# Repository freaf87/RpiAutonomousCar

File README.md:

Rpi Autonomous Car PCB 
====================
This board bring those additional functions below to the Raspberry pi:

	 - Analog Digital Converter with MCP3008 (8)
	 - DC Brushed Motor driver (2) with TB6612FNG
	 - Level converted IOs (5V <-> 3.3V) (8)
     - 16-channel, 12-bit PWM with PCA9685
     - RGB LED (1)
     - Pushbutton (1)

Top                                                                      |  Bottom
:-----------------------------------------------------------------------:|:--------------------------------------------------------------:
  |  

Author: Frederic Afadjigla, 2018

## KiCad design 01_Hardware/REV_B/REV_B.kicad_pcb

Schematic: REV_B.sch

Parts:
C1, C3: 100n; C_0603_1608Metric
C2: 10u; CP_Elec_4x4.5
C4, C5, C6, C7, C8, C9, C10, C11, C13: 10n; C_0603_1608Metric
C12: 0.33u; C_0603_1608Metric
J1: RaspberryPi; PinSocket_2x20_P2.54mm_Vertical
J2, J3, J4: Conn_01x02; Molex_KK-254_AE-6410-02A_1x02_P2.54mm_Vertical
J5: Conn_01x08; PinHeader_1x08_P2.54mm_LongPad_Vertical_SMD_Pin1Right
J6: Conn_02x04_Counter_Clockwise; PinHeader_2x04_P2.54mm_Vertical_SMD
J7, J8, J9, J10, J11, J12: Conn_01x03; PinHeader_1x03_P2.54mm_Vertical
J13: Conn_01x08; PinHeader_1x08_P2.54mm_Vertical
J14: Conn_01x01; PinSocket_1x01_P2.54mm_Vertical
JP1: Jumper_3_Open; SolderJumper-3_P1.3mm_Open_RoundedPad1.0x1.5mm
R1, R2, R3, R4, R10, R11, R12, R13, R48: 1k; R_0603_1608Metric
R5, R6, R7, R8, R9, R30, R31, R32, R33, R34, R35, R36, R37, R38, R39, R40, R41, R42, R43, R44, R45: 10k; R_0603_1608Metric
R14, R15, R16, R17: 22k; R_0603_1608Metric
R18, R19, R20, R21, R22, R23, R24, R25, R26, R27, R28, R29, R46, R47: 220; R_0603_1608Metric
SW1: SW_Push; SW_PUSH_6mm
U1: TB6612FNG; SSOP-24_5.3x8.2mm_P0.65mm
U2: MCP3008; SOIC-16_3.9x9.9mm_P1.27mm
U3: PCA9685PW; TSSOP-28_4.4x9.7mm_P0.65mm
U4, U5, U6, U7: BSS138PS; SOT-363_SC-70-6
U8: L7805; TO-252-3_TabPin2
U9: ASMT-YTB7-0AA02; LED_Avago_PLCC6_3x2.8mm

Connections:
+3V3: C1.1, J1.1, J1.17, J11.1, J11.2, J11.3, R30.1, R31.1, R32.1, R33.1, R34.1, R35.1, R36.1, R37.1, SW1.2, U1.20, U2.15 (Vref), U2.16 (Vdd), U4.2, U4.5, U5.2, U5.5, U6.2, U6.5, U7.2, U7.5
+5V: C13.1, J1.2, J1.4, J7.2, J8.2, J9.2, J10.1, J10.2, J10.3, JP1.3, R38.1, R39.1, R40.1, R41.1, R42.1, R43.1, R44.1, R45.1, U3.3, U3.5, U3.28, U8.3
+BATT: C2.1, C3.1, C12.1, J2.2, J14.1, U1.13, U1.14, U1.24, U8.1
GND: C1.2, C2.2, C3.2, C4.2, C5.2, C6.2, C7.2, C8.2, C9.2, C10.2, C11.2, C12.2, C13.2, J1.6, J1.9, J1.14, J1.20, J1.25, J1.30, J1.34, J1.39, J2.1, J7.3, J8.3, J9.3, J12.1, J12.2, J12.3, JP1.1, R1.2, R2.2, R3.2, R4.2, R5.2, R6.2, R7.2, R8.2, R9.1, U1.3, U1.4, U1.9, U1.10, U1.18, U2.9 (DGND), U2.14 (AGND), U3.1, U3.2, U3.4, U3.14, U3.25, U8.2, U9.1, U9.2, U9.3
I2C1_SCL_HV: J13.2, R43.2, U3.26, U5.3
I2C1_SCL_LV: J1.5, R33.2, U5.4
I2C1_SDA_HV: J13.1, R39.2, U3.27, U5.6
I2C1_SDA_LV: J1.3, R32.2, U5.1
unnamed: C4.1, R1.1, R10.2, U2.1 (CH0)
unnamed: C5.1, R2.1, R11.2, U2.2 (CH1)
unnamed: C6.1, R3.1, R12.2, U2.3 (CH2)
unnamed: C7.1, R4.1, R13.2, U2.4 (CH3)
unnamed: C8.1, R5.1, R14.2, U2.5 (CH4)
unnamed: C9.1, R6.1, R15.2, U2.6 (CH5)
unnamed: C10.1, R7.1, R16.2, U2.7 (CH6)
unnamed: C11.1, R8.1, R17.2, U2.8 (CH7)
unnamed: J1.24, U2.10 (~CS~/SHDN)
unnamed: J1.32, U1.23
unnamed: J1.33, U1.15
unnamed: J1.35, U1.21
unnamed: J1.36, U1.22
unnamed: J1.37, U1.17
unnamed: J1.38, U1.16
unnamed: J1.40, U1.19
unnamed: J3.1, U1.1, U1.2
unnamed: J3.2, U1.5, U1.6
unnamed: J4.1, U1.11, U1.12
unnamed: J4.2, U1.7, U1.8
unnamed: J5.1, R10.1
unnamed: J5.2, R11.1
unnamed: J5.3, R12.1
unnamed: J5.4, R13.1
unnamed: J5.5, R14.1
unnamed: J5.6, R15.1
unnamed: J5.7, R16.1
unnamed: J5.8, R17.1
unnamed: J6.1, R21.1
unnamed: J6.2, R22.1
unnamed: J6.3, R23.1
unnamed: J6.4, R24.1
unnamed: J6.5, R25.1
unnamed: J6.6, R26.1
unnamed: J6.7, R27.1
unnamed: J6.8, R28.1
unnamed: J7.1, R47.1
unnamed: J8.1, R46.1
unnamed: J9.1, R29.1
unnamed: J13.3, R38.2, U4.6
unnamed: J13.4, R42.2, U4.3
unnamed: J13.5, R40.2, U6.6
unnamed: J13.6, R44.2, U6.3
unnamed: J13.7, R41.2, U7.6
unnamed: J13.8, R45.2, U7.3
unnamed: JP1.2, U3.24
unnamed: R9.2, U3.23
unnamed: R18.1, U9.6
unnamed: R18.2, U3.22
unnamed: R19.1, U9.5
unnamed: R19.2, U3.21
unnamed: R20.1, U9.4
unnamed: R20.2, U3.20
unnamed: R21.2, U3.6
unnamed: R22.2, U3.7
unnamed: R23.2, U3.8
unnamed: R24.2, U3.9
unnamed: R25.2, U3.10
unnamed: R26.2, U3.11
unnamed: R27.2, U3.12
unnamed: R28.2, U3.13
unnamed: R29.2, U3.15
unnamed: R46.2, U3.16
unnamed: R47.2, U3.17
unnamed: R48.2, SW1.1
PUSH_BUTTON: J1.22, R48.1
SPI0_CLK_LV: J1.23, R34.2, U2.13 (CLK), U6.1
SPI0_CS1_LV: J1.26, R35.2, U6.4
SPI0_MISO_LV: J1.21, R31.2, U2.12 (Dout), U4.4
SPI0_MOSI_LV: J1.19, R30.2, U2.11 (Din), U4.1
UART_RX_LV: J1.10, R37.2, U7.4
UART_TX_LV: J1.8, R36.2, U7.1

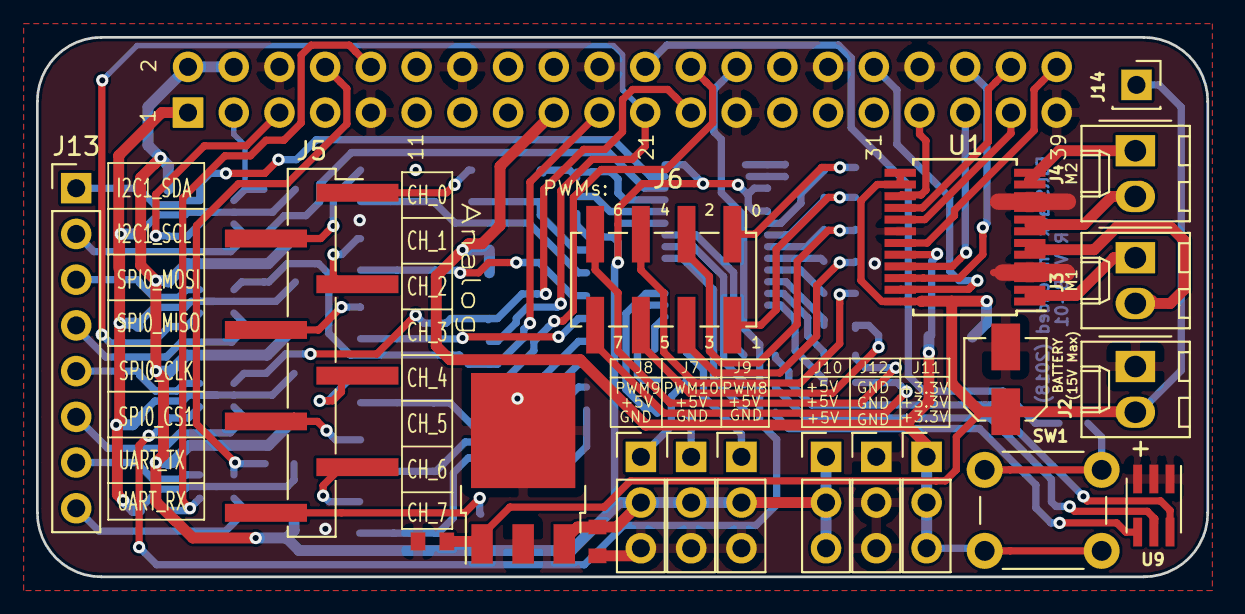
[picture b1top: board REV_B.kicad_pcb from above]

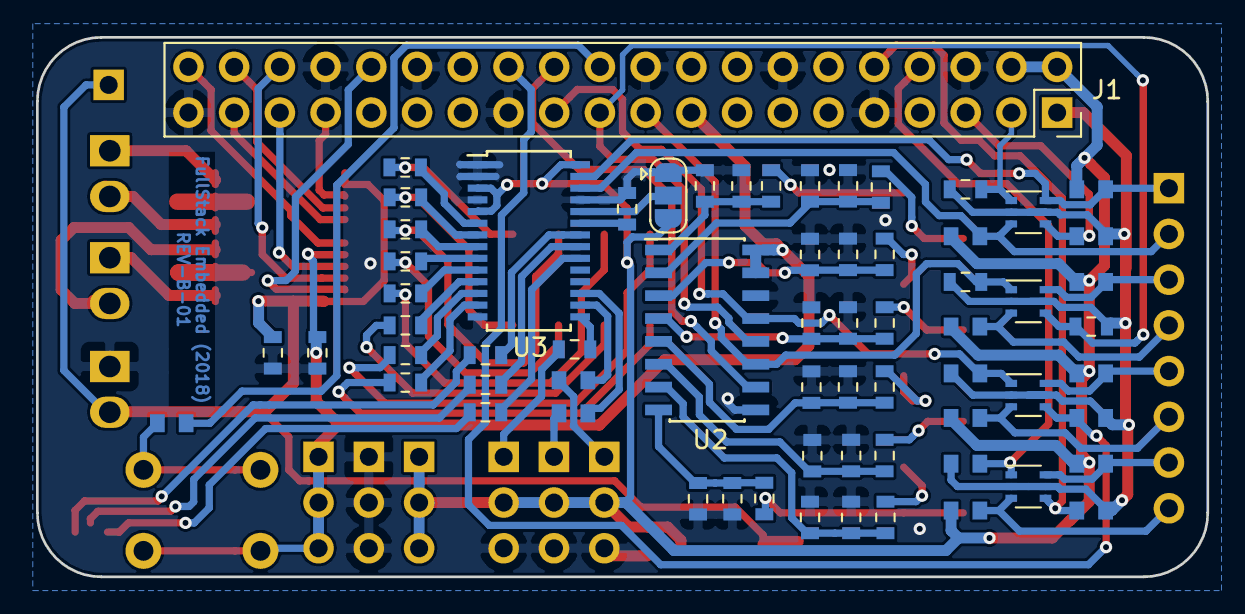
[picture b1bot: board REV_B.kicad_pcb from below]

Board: 2 copper layers, 65.0 x 30.0 mm, 86 parts (66 on the bottom side), 80 nets.

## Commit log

2017-05-01 routing...
2017-05-13 routing
2017-05-26 routing ...
2017-05-29 rounting/Pinout minor changes
2017-05-29 routing almost done
2017-05-30 routing done
2017-06-05 ready for review
2017-06-07 routing done. Ready to order
2017-06-10 Version 1 done
2017-06-11 Hardware Documentation added
2017-06-13 Documenting...
2017-06-17 Restructure Directories
2017-06-18 add cost calculation
2017-06-24 driver HCSR04 LED MCP3004 TB6612FNG added
2017-06-24 moinor corrections
2017-06-24 servo driver added
2017-06-28 add simple autonomous program
2017-07-09 Remote control added
2017-08-05 minor changes
2017-08-18 Docu actualised
2017-09-15 Thread based Line follower added
2017-09-23 Line follower (continued)
2017-10-28 Refactor and add TODOs
2017-10-28 Add test of drive function
2017-10-28 Implement turning
2017-10-29 Add ultrasonic current measurement property
2017-10-29 Add obstacle detection test
2017-10-29 Add curve driving function
2017-10-29 Add option to skip tests
2017-10-30 Hardware PWM support
2017-10-31 Add shebangs, encoding and license headers
2017-10-31 Use new API for autonomous driving
2017-10-31 Use continuous drive mode
2017-10-31 Rename for PEP8
2017-10-31 Perform complete rotation to keep from tangling code in test
2017-10-31 Remove unused file
2017-10-31 Refactor ultrasonic ranger
2017-10-31 Migrate to wiringpi
2017-11-02 Call builtin debug rather than self-made
2017-11-02 Establish connection within Receiver class
2017-11-02 Move connection closing into class
2017-11-02 Have class start thread on its own
2017-11-02 Simplify command sending logic
2017-11-02 Close connection through context manager
2017-11-02 PEP8 and light refactor of LED
2017-11-02 Move GPIO bookkeeping into superclass
2017-11-02 Subclass LED to GPIO_Manager
2017-11-02 Factor distance measurements into properties
2017-11-02 Migrate infrared sensor to subclass GPIO_Manager
2017-11-02 Move hardware modules into their own package
2017-11-04 Use INPUT/OUTPUT constants from wiringpi
2017-11-04 Use __exit__ rather than destroy methods
2017-11-04 Migrate to motor_driver to wiringpi
2017-11-04 Add LED test, reorganize controllers
2017-11-04 Roll code into package
2017-11-04 HW Pwm modifications
2017-11-04 Insert headers, rename files
2017-11-04 Refactor LineFollowers
2017-11-05 Refactor ADC code
2017-11-05 Use Robot in LineFollower
2017-11-05 Use correct constant
2017-11-05 Naming refactor
2017-11-05 Finish renaming
2017-11-05 Further refactoring of TB6612FNG
2017-11-05 Correct typo
2017-11-12 Fix TB6612FNG driver
2017-11-12 Migrate to hardware PWM
2017-11-12 Refactoring
2017-11-12 Add infrared interface to Robot
2017-11-12 Add dependencies
2017-11-12 Simplify LineFollower
2017-11-12 Check for sudo in MotorDriver
2017-11-12 Adjust duty cycle
2017-11-12 typo
2017-11-12 Bugfix
2017-11-12 Adjust Robot's duty cycle
2017-11-12 Use absolute, not relative imports
2017-11-12 Add long description to setup.py
2017-11-12 Business as usual when no obstacle found
2017-11-12 Fix bug in line follower
2017-11-12 Proper exit for LineFollower
2017-11-12 Improve line following
2017-11-12 Finalize remote control
2017-12-03 Pass through non-sudoer error for tests
2017-12-03 Properly register motor driver pins
2018-01-21 (1) Changes from Lome and Ghana (2) Board Revision B started
2018-01-28 Designing RevB
2018-02-04 Work in Progress
2018-02-04 Brd redo due to kicad update
2018-02-25 Set theme jekyll-theme-dinky
2018-04-04 kicad version REVB added
2018-04-22 Routing started
2018-04-23 Reorder
2018-04-24 remaning resistors added to PCA9685 w/ routing
2018-04-30 Routing in progress
2018-05-27 Taster added. routing not done
2018-06-08 Routing done. Ready to be manufactured
2018-06-09 Last Modification: Jumper J5 long pad smd used
2018-08-11 Motor driver updated
2018-08-12 ADC and PWM Driver completed
2018-09-30 REVB-02 implemented. (1) Rpi header mirrored (2) New Switch added (THR) (3) New RGB LED
